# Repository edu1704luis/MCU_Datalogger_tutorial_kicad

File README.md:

# KiCad Learning Project: [MCU Datalogger]

This repository documents my progress through the **"KiCad Like a Pro"** curriculum by **Peter Dalmaris**. 

The goal of this project is to practice professional PCB design workflows, moving from a theoretical schematic to a physical, manufacturable board.

## ⚖️ Authorship & Attribution
To maintain transparency regarding intellectual property:

* **Circuit Design & Schematic:** The circuit logic and schematic diagrams are based on the designs provided by Peter Dalmaris in "KiCad Like a Pro" (Tech Explorations). All credit for the electrical engineering and circuit concept goes to the original author.
* **PCB Layout & Routing:** The physical board layout, component placement, and trace routing contained in this repository are my own work, performed as an educational exercise following the book's guidelines.

## 📚 Reference Material
* **Source:** [KiCad Like a Pro](https://techexplorations.com/kicad-like-a-pro-3rd-edition-reference/) by Peter Dalmaris.
* **Tools Used:** KiCad EDA.

## 🛠️ Repository Content
* `/schematics`: My reproduction of the book's circuit diagrams.
* `/pcb_layout`: My personal implementation of the PCB design, including routing and board geometry.
* `/renders`: 3D visualizations of the finished board design.

## 📜 License
The files generated by me in this repository are shared under the **MIT License**. This project is intended for educational and portfolio purposes only. 

---
*Disclaimer: This repository is an independent study project and is not affiliated with or endorsed by Tech Explorations.*

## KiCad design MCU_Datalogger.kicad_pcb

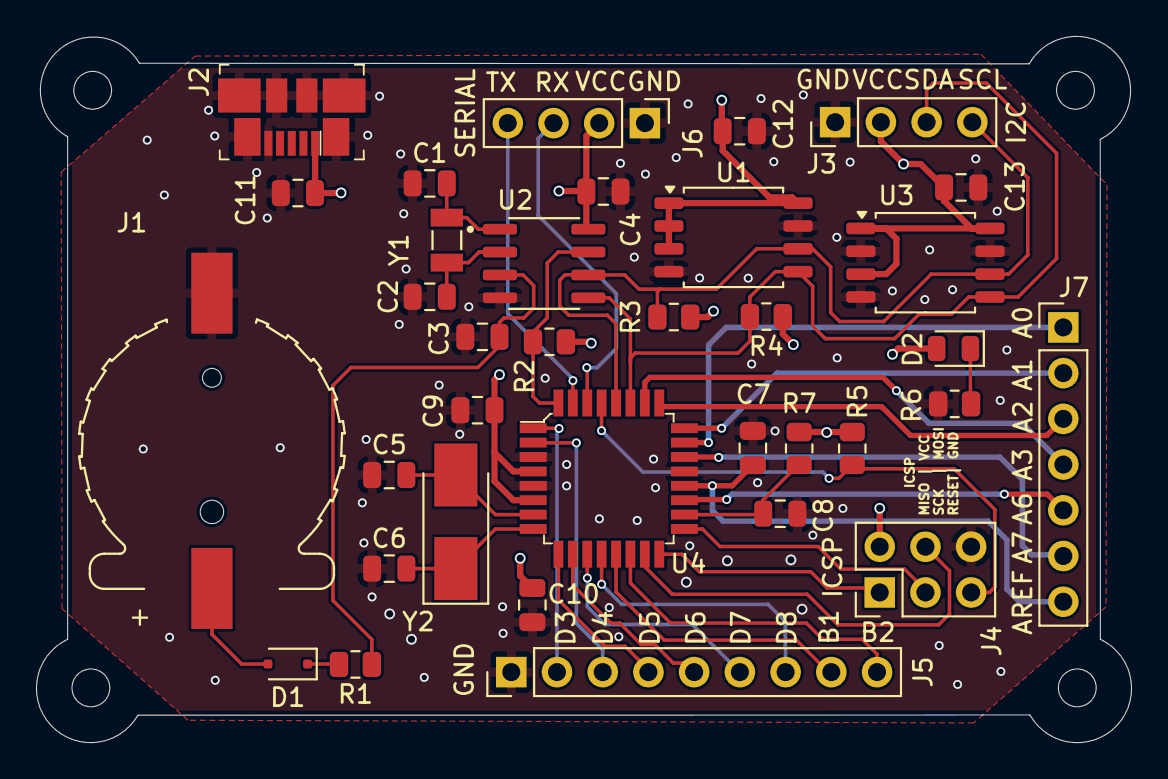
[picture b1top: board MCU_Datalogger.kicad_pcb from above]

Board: 4 copper layers, 60.8 x 39.2 mm, 39 parts (0 on the bottom side), 35 nets.

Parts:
C1, C2: 10pF; C_0805_2012Metric
C3: 100pF; C_0805_2012Metric
C4, C7: 0.1uF; C_0805_2012Metric
C5, C6: 22pF; C_0805_2012Metric
C8, C9, C10, C12, C13: 100nF; C_0805_2012Metric
C11: 10uF; C_0805_2012Metric
D1: BAT54J; D_SOD-323F
D2: LED; LED_0805_2012Metric
H1, H2, H3, H4: MountingHole; MountingHole_2.1mm
J1: S8411-45R; HARWIN_S8411-45R
J2: USB_B_Micro; USB_Micro_B_Female_6pin
J3, J6: Conn_01x04; PinHeader_1x04_P2.54mm_Vertical
J4: Conn_02x03_Odd_Even; PinHeader_2x03_P2.54mm_Vertical
J5: Conn_01x09; PinHeader_1x09_P2.54mm_Vertical
J7: Conn_01x07; PinHeader_1x07_P2.54mm_Vertical
R1: 1k; R_0805_2012Metric
R2, R3, R4: 4.7K; R_0805_2012Metric
R5: 10K; R_0805_2012Metric
R6: 330; R_0805_2012Metric
R7: 10; R_0805_2012Metric
U1, U3: 24LC1025; SOIC-8_5.3x5.3mm_P1.27mm
U2: MCP7940NT-I_SN; SOIC127P600X175-8N
U4: ATMEGA328P-AU; TQFP-32_7x7mm
Y1: 32.768 KHz; XTAL_FC-135_32.7680KA-A0
Y2: 16 MHz; Crystal_SMD_5032-2Pin_5.0x3.2mm_HandSoldering

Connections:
/ADC0: J7.1, U4.23 (PC0)
/ADC1: J7.2, U4.24 (PC1)
/ADC2: J7.3, U4.25 (PC2)
/ADC3: J7.4, U4.26 (PC3)
/ADC6: J7.5, U4.19 (ADC6)
/ADC7: J7.6, U4.22 (ADC7)
/AREF: C7.1, J7.7, U4.20 (AREF)
/B1: J5.8, U4.13 (PB1)
/B2/SS: J5.9, U4.14 (PB2)
/D3: J5.2, U4.1 (PD3)
/D4: J5.3, U4.2 (PD4)
/D5: J5.4, U4.9 (PD5)
/D6: J5.5, U4.10 (PD6)
/D7: J5.6, U4.11 (PD7)
/D8: J5.7, U4.12 (PB0)
/MFP: R2.2, U2.7 (MFP), U4.32 (PD2)
/MISO: J4.1, U4.16 (PB4)
/MOSI: J4.4, U4.15 (PB3)
/RESET: J4.5, R5.2, U4.29 (PC6)
/RX: J6.3, U4.30 (PD0)
/SCK: J4.3, U4.17 (PB5)
/SCL: J3.4, R3.2, U1.6 (SCL), U2.6 (SCL), U3.6 (SCL), U4.28 (PC5)
/SDA: J3.3, R4.2, U1.5 (SDA), U2.5 (SDA), U3.5 (SDA), U4.27 (PC4)
/TX: J6.4, U4.31 (PD1)
/Vcc: C4.1, C9.1, C10.1, C11.1, C12.2, C13.1, D2.2 (A), J2.1 (VBUS), J3.2, J4.2, J6.2, R2.1, R3.1, R4.1, R5.1, R7.2, U1.1 (A0), U1.2 (A1), U1.3 (A2), U1.8 (VCC), U2.8 (VCC), U3.1 (A0), U3.3 (A2), U3.8 (VCC), U4.4 (VCC), U4.6 (VCC)
GND: C1.1, C2.1, C3.2, C4.2, C5.1, C6.1, C7.2, C8.2, C9.2, C10.2, C11.2, C12.1, C13.2, J1.N, J2.5 (GND), J2.6 (Shield), J3.1, J4.6, J5.1, J6.1, R6.2, U1.4 (GND), U1.7 (WP), U2.4 (VSS), U3.2 (A1), U3.4 (GND), U3.7 (WP), U4.3 (GND), U4.5 (GND), U4.21 (GND)
unnamed: D1.2 (A), J1.P
unnamed: D1.1 (K), R1.2
unnamed: D2.1 (K), R6.1
unnamed: C3.1, R1.1, U2.3 (VBAT)
unnamed: C1.2, U2.1 (X1), Y1.2
unnamed: C2.2, U2.2 (X2), Y1.1
unnamed: C8.1, R7.1, U4.18 (AVCC)
unnamed: C5.2, U4.7 (PB6), Y2.2
unnamed: C6.2, U4.8 (PB7), Y2.1

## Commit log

2026-01-15 Init project.
2026-01-16 Create README
    readme text
2026-01-16 added symbols to the schematic sheets
2026-01-17 Schematic Complete
2026-01-17 Schematic ok
2026-01-17 Setup PCB
2026-01-21 Some changes to the original design of the kicad book
2026-01-26 Complete 2-layer pcb
2026-01-28 Complete 4-layer pcb
2026-01-28 Restore Schematic from 2layer
